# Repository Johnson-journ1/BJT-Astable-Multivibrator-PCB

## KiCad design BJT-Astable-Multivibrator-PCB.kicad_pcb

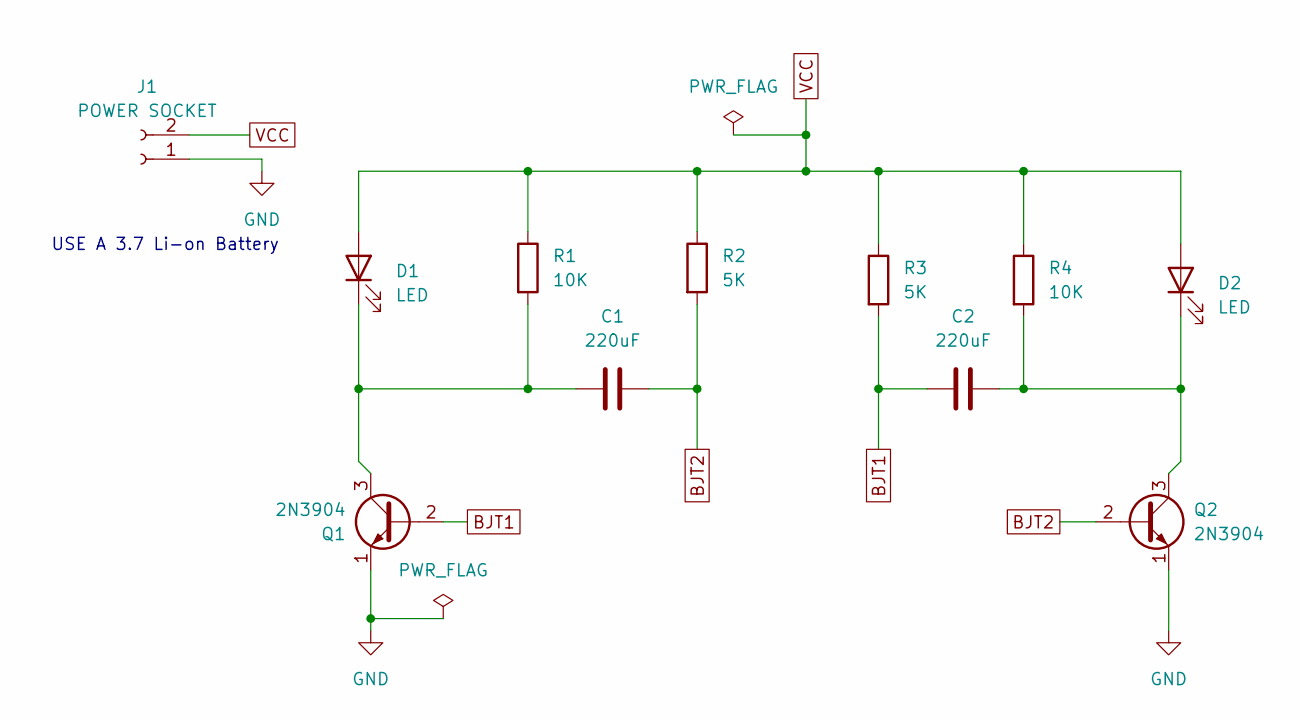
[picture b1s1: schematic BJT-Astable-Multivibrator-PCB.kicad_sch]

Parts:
C1, C2: 220uF; C_Disc_D3.0mm_W1.6mm_P2.50mm
D1, D2: LED; LED_D3.0mm
J1: POWER SOCKET; PinHeader_1x02_P2.54mm_Vertical
Q1, Q2: 2N3904; TO-92_Inline
R1, R4: 10K; R_Axial_DIN0204_L3.6mm_D1.6mm_P1.90mm_Vertical
R2, R3: 5K; R_Axial_DIN0204_L3.6mm_D1.6mm_P1.90mm_Vertical

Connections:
BJT1: C2.1, Q1.2 (B), R3.2
BJT2: C1.2, Q2.2 (B), R2.2
GND: J1.1, Q1.1 (E), Q2.1 (E)
unnamed: C1.1, D1.1 (K), Q1.3 (C), R1.2
unnamed: C2.2, D2.1 (K), Q2.3 (C), R4.2
VCC: D1.2 (A), D2.2 (A), J1.2, R1.1, R2.1, R3.1, R4.1

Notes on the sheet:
USE A 3.7 Li-on Battery

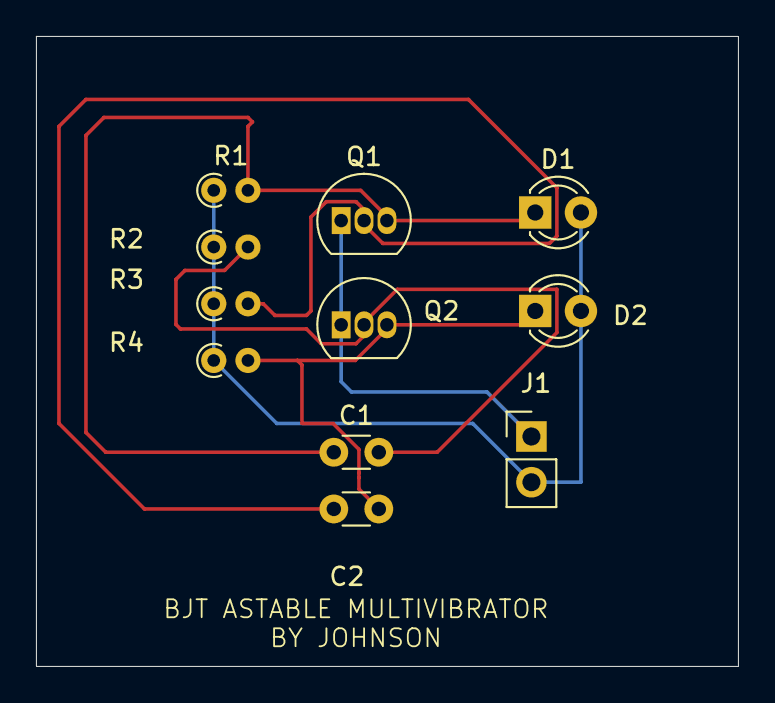
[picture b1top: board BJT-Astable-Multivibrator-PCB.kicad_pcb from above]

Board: 2 copper layers, 39.0 x 35.0 mm, 11 parts (0 on the bottom side), 6 nets.
